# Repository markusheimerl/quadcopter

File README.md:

# quadcopter
A quadcopter simulation & hardware design

Consider a quadcopter modeled as a rigid body with state $(\mathbf{p}, \mathbf{v}, R, \boldsymbol{\omega})$, where $\mathbf{p}, \mathbf{v} \in \mathbb{R}^3$ are the position and linear velocity in the world frame $W$, $R \in SO(3)$ is the body-to-world rotation, and $\boldsymbol{\omega} \in \mathbb{R}^3$ is the angular velocity in the body frame $B$. The world frame is right-handed with $\mathbf{e}_y$ pointing up, and the body frame is defined with $\mathbf{x}_B$ forward, $\mathbf{y}_B$ along the thrust axis, and $\mathbf{z}_B$ to the right. The four rotors sit in an X-configuration at body positions $(x_i, 0, z_i) = (\pm a, 0, \pm a)$, with alternating CCW/CW spin directions $s_i \in \{+1, -1\}$. Each rotor produces a thrust $f_i = k_F \omega_i^2$ along $+\mathbf{y}_B$ and an aerodynamic drag torque $m_i = k_M \omega_i^2$ about $\mathbf{y}_B$. The total body-frame thrust magnitude $T$ and torque $\boldsymbol{\tau} \in \mathbb{R}^3$ are:

$$
\begin{align*}
T &= \sum_{i=0}^{3} k_F \omega_i^2 \\
\tau_x &= \sum_{i=0}^{3} -z_i \, k_F \omega_i^2 \\
\tau_y &= \sum_{i=0}^{3} s_i \, k_M \omega_i^2 \\
\tau_z &= \sum_{i=0}^{3} x_i \, k_F \omega_i^2
\end{align*}
$$

The rigid-body equations of motion are Newton's second law in the world frame and Euler's equation in the body frame. With mass $m$, gravitational acceleration $g$, and diagonal inertia $I = \mathrm{diag}(I_{xx}, I_{yy}, I_{zz})$:

$$
\begin{align*}
\dot{\mathbf{p}} &= \mathbf{v} \\
\dot{\mathbf{v}} &= \tfrac{T}{m} R \mathbf{e}_y - g \mathbf{e}_y \\
\dot{R} &= R [\boldsymbol{\omega}]_\times \\
I \dot{\boldsymbol{\omega}} &= \boldsymbol{\tau} - \boldsymbol{\omega} \times I \boldsymbol{\omega}
\end{align*}
$$

Here $[\boldsymbol{\omega}]_\times$ is the skew-symmetric matrix associated with $\boldsymbol{\omega}$. The simulator integrates these equations at $1\,\mathrm{kHz}$ using a semi-implicit (symplectic) Euler scheme: velocities are advanced first, then positions and attitude are updated with the new velocities. The attitude update uses the exact exponential map on $SO(3)$ with the midpoint angular velocity, evaluated via Rodrigues' formula:

$$
\begin{align*}
\boldsymbol{\phi} &= \tfrac{1}{2} \Delta t (\boldsymbol{\omega}_k + \boldsymbol{\omega}_{k+1}) \\
\mathbf{v}_{k+1} &= \mathbf{v}_k + \Delta t \left( \tfrac{T}{m} R_k \mathbf{e}_y - g \mathbf{e}_y \right) \\
\boldsymbol{\omega}_{k+1} &= \boldsymbol{\omega}_k + \Delta t \, I^{-1} \left( \boldsymbol{\tau} - \boldsymbol{\omega}_k \times I \boldsymbol{\omega}_k \right) \\
\mathbf{p}_{k+1} &= \mathbf{p}_k + \Delta t \, \mathbf{v}_{k+1} \\
R_{k+1} &= R_k \exp\!\left( [\boldsymbol{\phi}]_\times \right) \\
\exp\!\left( [\boldsymbol{\phi}]_\times \right) &= I_3 + \tfrac{\sin\|\boldsymbol{\phi}\|}{\|\boldsymbol{\phi}\|} [\boldsymbol{\phi}]_\times + \tfrac{1 - \cos\|\boldsymbol{\phi}\|}{\|\boldsymbol{\phi}\|^2} [\boldsymbol{\phi}]_\times^2
\end{align*}
$$

For small $\|\boldsymbol{\phi}\|$ the coefficients are replaced by their Taylor expansions $\sin(t)/t \approx 1 - t^2/6$ and $(1-\cos t)/t^2 \approx 1/2 - t^2/24$ to avoid the $0/0$ singularity. A rigid floor constraint clamps $p_y \ge 0$ and zeros downward velocity on contact.

The flight controller is a geometric tracking controller on $SO(3)$ running at $100\,\mathrm{Hz}$, given a target state $\mathbf{x}\_d = (\mathbf{p}\_d, \mathbf{v}\_d, \psi\_d)$. Position and velocity errors drive a desired world-frame force, from which a desired thrust direction $\mathbf{b}\_{2,d}$ is extracted. The thrust magnitude is projected onto the current body-Y axis $\mathbf{b}\_2 = R \mathbf{e}\_y$ to decouple thrust from tilt error:

$$
\begin{align*}
\mathbf{e}_p &= \mathbf{p} - \mathbf{p}_d \\
\mathbf{e}_v &= \mathbf{v} - \mathbf{v}_d \\
\mathbf{F} &= -K_p \mathbf{e}_p - K_v \mathbf{e}_v + m g \mathbf{e}_y \\
\mathbf{b}_{2,d} &= \frac{\mathbf{F}}{\|\mathbf{F}\|} \\
T &= \max\!\left(0,\; \mathbf{F} \cdot \mathbf{b}_2 \right)
\end{align*}
$$

A heading reference $\mathbf{c} = (\cos\psi_d,\, 0,\, -\sin\psi_d)$ defines the desired yaw, and the remaining body axes are obtained by orthogonalization:

$$
\begin{align*}
\mathbf{b}_{3,d} &= \frac{\mathbf{c} \times \mathbf{b}_{2,d}}{\|\mathbf{c} \times \mathbf{b}_{2,d}\|} \\
\mathbf{b}_{1,d} &= \mathbf{b}_{2,d} \times \mathbf{b}_{3,d} \\
R_d &= [\mathbf{b}_{1,d} \;\; \mathbf{b}_{2,d} \;\; \mathbf{b}_{3,d}]
\end{align*}
$$

The attitude and angular-velocity errors in the body frame, together with the feedback-linearized control torque, follow:

$$
\begin{align*}
\mathbf{e}_R &= \tfrac{1}{2} \left( R_d^T R - R^T R_d \right)^{\vee} \\
\mathbf{e}_\omega &= \boldsymbol{\omega} \\
\boldsymbol{\tau} &= -K_R \mathbf{e}_R - K_\omega \mathbf{e}_\omega + \boldsymbol{\omega} \times I \boldsymbol{\omega}
\end{align*}
$$

where $(\cdot)^{\vee}$ is the inverse of $[\cdot]_\times$, extracting the axial vector from a skew-symmetric matrix. Finally, the desired thrust and torque are mapped to squared rotor speeds by inverting the linear X-configuration mixer $[T, \tau_x, \tau_y, \tau_z]^T = M [\omega_0^2, \omega_1^2, \omega_2^2, \omega_3^2]^T$:

$$
\begin{align*}
\omega_0^2 &= \tfrac{T}{4 k_F} - \tfrac{\tau_x}{4 a k_F} + \tfrac{\tau_y}{4 k_M} + \tfrac{\tau_z}{4 a k_F} \\
\omega_1^2 &= \tfrac{T}{4 k_F} - \tfrac{\tau_x}{4 a k_F} - \tfrac{\tau_y}{4 k_M} - \tfrac{\tau_z}{4 a k_F} \\
\omega_2^2 &= \tfrac{T}{4 k_F} + \tfrac{\tau_x}{4 a k_F} + \tfrac{\tau_y}{4 k_M} - \tfrac{\tau_z}{4 a k_F} \\
\omega_3^2 &= \tfrac{T}{4 k_F} + \tfrac{\tau_x}{4 a k_F} - \tfrac{\tau_y}{4 k_M} + \tfrac{\tau_z}{4 a k_F} \\
\omega_i &= \mathrm{clip}\!\left( \sqrt{\max(0, \omega_i^2)},\; \omega_{\min},\; \omega_{\max} \right)
\end{align*}
$$

The commanded rotor speeds are clamped to $[\omega_{\min}, \omega_{\max}]$ before being applied to the dynamics. The implementation runs physics at $1\,\mathrm{kHz}$, control at $100\,\mathrm{Hz}$, and renders frames through a CPU raytracer at $24\,\mathrm{fps}$.

## Hardware

The flight controller / frame PCB lives in [pcb/](pcb/) as a [tscircuit](https://tscircuit.com) design with a JLCPCB-ready build (`npm run fab`). Firmware for it is in [firmware/](firmware/). Older EasyEDA designs are kept in [hardware/](hardware/).

## How to run
### Ubuntu
```bash
sudo apt update
sudo apt install -y clang make git
git clone https://github.com/markusheimerl/quadcopter && cd quadcopter/
make run -j 6
```

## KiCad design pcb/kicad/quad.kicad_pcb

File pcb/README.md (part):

# quad pcb

Flight controller and frame on a single 2‑layer PCB, written in
[tscircuit](https://tscircuit.com). `index.tsx` is the whole design: parts,
schematic, placement and every copper track (drawn by hand, no autorouter).
The four arms are the frame; the electronics sit in the 44.8 mm core. Each
motor connector sits in its corner with the cable opening facing down the arm.

Schematic: [img/schematic.svg](img/schematic.svg) · KiCad files (to look
around, measure, run DRC/ERC): [kicad/](kicad/).

## Order it (no install needed)

The ready‑made files are in [fab/](fab/). On jlcpcb.com:

1. *Order now* → upload `fab/gerbers.zip`. The viewer should show a
   75.12 × 75.12 mm, 2‑layer board with the USB‑C slots drawn. 1.6 mm, FR‑4,
   any colour. Via covering: *tented* (the default). Surface finish: the
   form defaults to leaded HASL – pick lead‑free HASL, or ENIG (flatter pads
   for the IMU's 0.5 mm LGA). *Remove order number*: choose *Specify a
   location* – the back has a `JLCJLCJLCJLC` spot for it.
2. Tick *PCB Assembly*, top side, **Standard** (the ESP32 module and the IMU
   are Standard‑only; about $170 for assembly and parts of 5 boards, Sep
   2026). Upload `fab/bom.csv` and `fab/cpl.csv`. Every row has its JLCPCB
   part number and all are in stock. Seven are *extended* parts (module,
   IMU, TPS63001, inductor, the three connector types), the rest *basic* or
   *preferred* – which only matters for Economic PCBA: Standard charges the
   same feeder fee (about $1.53) for each of the 26 BOM lines. Tick *Confirm
   production file* and look at the panel drawing before it goes into
   production.
3. Order remark: "The ESP32 module and the USB‑C socket overhang the nose
   and tail edges on purpose. Break‑off tabs only on the end faces of the
   arms – none on the curved core outline (the motor connectors, C13 and
   both buttons are within 0.45 mm of it). Please cut the stencil from our
   F_Paste layer." Standard PCBA always adds rails and fiducials; file the
   tab nubs at the arm tips flush before fitting the motor clips.
4. In the placement preview check each part once: antenna toward the nose,
   USB‑C opening at the tail edge, the diode bands (cathode) on the inner end
   of D1–D4 where each diode meets its VBAT rail, LED anodes toward their 1 k
   resistor (LED1 → R11, LED2 → R17), the IMU's pin‑1 dot (top‑left corner),
   U3's pin 1 at the silkscreen dot (top‑left, toward the inductor), U4 pin 1.
   `cpl.csv` already places every part at JLCPCB's own footprint origin.

## What is on it

| Block | Part | JLCPCB # |
|---|---|---|
| MCU | ESP32‑S3‑WROOM‑1‑N16R8, antenna over the nose edge | C2913202 |
| IMU | BMI323, I2C at 0x68, +X = nose, +Y = left, +Z = up | C5368700 |
| Motor drive ×4 | AO3400A low‑side, 47 Ω gate, 10 k pull‑down, B5819W flyback | C20917, C8598 |
| Motor connectors ×4 | HC‑1.25‑2PWT (1.25 mm, 2 pin), "+" marked on the silkscreen | C2845379 |
| Battery | Molex PicoBlade 53398‑0271, "+"/"−" marked, 100 µF bulk | C122410, C15008 |
| 3.3 V | TPS63001 buck‑boost: 3.3 V from 1.8–5.5 V in (1.2 A buck, 0.8 A boost), always on, power‑save mode at light load, 2.2 µH | C28060, C5832372 |
| Charger | TP4054, 190 mA (R16 = 5.1 k, datasheet formula 1), CHG LED | C32574 |
| USB | USB‑C, native S3 USB (flashing + console), 5.1 k CC pull‑downs | C2765186 |
| Buttons | RST (EN, left edge) and BOOT (IO0, right edge), top‑actuated | C720477 |
| Battery sense | VBAT / 2 on IO10 (100 k / 100 k, 100 nF) | |
| UART pads | TX, RX, GND on the back (TP1–TP3) | |

Pin map (also on the schematic, and in `firmware/main/main.c`):

| GPIO | Use |
|---|---|
| IO1, IO2, IO16, IO4 | PWM0–3 → M0 front right, M1 back right, M2 back left, M3 front left (high = on) |
| IO11, IO12 | I2C SDA, SCL (BMI323) |
| IO10 | battery voltage / 2 (ADC1 channel 9, use 12 dB attenuation) |
| IO21 | LED1, active low |
| IO19, IO20 | USB D−, D+ |
| IO0 / EN | BOOT / RESET buttons |
| TXD0, RXD0 | UART0 pads TP1, TP2 |

Motors: FR and BL spin CCW, BR and FL spin CW (printed on each arm). The
connector pin marked "+" is VBAT; the other pin is switched to ground. The
pinout and the connector positions match the May 2026 board, so its motor
leads plug in the same way and reach just as far: each connector sits as far
out along its arm as its metal side tabs allow (0.33 mm from the curved
edge), its opening about 24.8 mm from the arm tip.
A brushed motor's direction follows its polarity – if one spins the wrong
way, swap its two wires.

Copper: bottom layer is a ground pour; VBAT runs 1 mm wide on top plus a
1.5 mm bus on the bottom from the battery connector; motor nets 0.6–0.8 mm;
vias 0.3/0.6 mm. The buck‑boost follows its datasheet layout: input and
output caps right at VIN/VOUT with their grounds straight into the exposed
pad, the inductor beside the VBAT rail, unbroken ground pour underneath
(the USB data pair runs past it, between converter and IMU).

The motor connectors' "+" pins match the May 2026 boards. The November 2025
board had front‑left and back‑right the other way round: leads made for that
board spin FL/BR backwards here. Check each motor's direction with the props
off (BLE keys `1`–`4`).

## Change the design

Needs Node ≥ 20; `npm install` brings everything else (including `bun`) and
applies the small tscircuit fixes in `scripts/patch-tscircuit.mjs`.

```bash
cd pcb
npm install
npm run build   # ~10 s: dist/circuit.json (board) + dist/sch.circuit.json (schematic), then DRC
npm run fab     # fab/gerbers.zip, fab/bom.csv, fab/cpl.csv
npm run kicad   # kicad/quad.kicad_pcb, .kicad_sch, .kicad_pro
npm run img     # img/pcb.png, img/schematic.svg
npm run place   # placement only (no copper) -> img/place.png
npm run dev     # live PCB / schematic / 3D view at http://localhost:3020
```

* `build.tsx` replaces `tsci build` (whose built‑in checks can hang). It
  renders the board twice: once with the copper for the PCB, once without it
  for the schematic, since tscircuit would otherwise draw the hand‑made PCB
  tracks into the schematic.
* `scripts/silk.ts` drops unprintable footprint texts and clips silkscreen
  lines 0.15 mm off pads, holes and the board edge (what JLCPCB would clip).
* `scripts/jlc.ts` writes the BOM and a CPL at JLCPCB's footprint origins
  (tscircuit's own pick‑and‑place uses pad centres, which is off for the
  module, USB‑C and connectors). `npm run fab` also puts each USB‑C slot's
  `G85` on one line in the drill file, as Excellon wants it.
* The exposed pad of U3 gets TI's stencil (two 1.5 × 1.06 mm openings at
  ±0.63 mm, 80 %)
  instead of a full opening, so the part doesn't float (`build.tsx`).
* `scripts/kicad.ts` touches up the KiCad export so KiCad reads it right:
  real power symbols, correct diode/connector pin numbers, net ties at
  junctions, no‑connect flags, JLCPCB design rules, text sizes as printed.
  The ground pour comes without fill: press **B** in KiCad to fill it.
* `footprints/` caches the JLCPCB footprints (some edited: USB‑C slots,
  a connector courtyard, TPS63001 exposed pad as TI's 1.65 × 2.4 mm land,
  inductor pads as its maker recommends),
  so builds work offline.
* `drc.py` is an independent check (`pip install shapely`): 0.2 mm copper
  clearance, 0.3 mm to the edge, via sizes, and that every net is one piece
  of copper: `python3 drc.py`.

## Checked before release

* tscircuit DRC (routing, placement, netlist, JLCPCB rules) and `drc.py`: clean.
* KiCad 9 DRC on the exported board with JLCPCB limits, zones refilled: clean;
  KiCad ERC on the schematic: clean.
* The netlist KiCad computes from the drawn schematic, and the connectivity
  extracted from the gerber copper + drill files, both equal the design
  netlist pin for pin (no opens, no shorts).
* Silkscreen in the gerbers: ≥ 0.15 mm from every pad and hole. Labels print
  about 1.0 mm tall with ≥ 0.16 mm strokes (BOOT 0.75 mm: it sits between a
  via and the edge); the "+"/"−" polarity marks are 1.0–1.2 mm lines.
* Every part checked against its datasheet (pinout vs footprint vs netlist,
  application circuit, ratings), each finding re‑checked independently.

## First power‑up

1. Meter every battery lead before its first plug‑in. Under the battery
   socket the silkscreen reads "+ − BAT": the pin above the "+" (the one
   farther from `BAT`) must get the pack's +. A reversed pack destroys the
   board. Motors go into the four arm sockets, the battery only into the
   `BAT` socket: a battery plug fits a motor socket too, and in two of them
   it shorts the pack through a diode.
2. Props off. Plug the battery in: LED1 blinks at 1 Hz within about 2 s
   (5 Hz: IMU not found; dark: the pack is below 3.0 V and the board sleeps
   – charge it – or look for a short or a dead 3.3 V). Nothing spins at
   power‑up.
3. Connect with `firmware/tools/motor_keys.py` (`pip install bleak`). It
   prints the status (reset reason, IMU id `0x..43`, level calibration,
   battery mV, trim, gain); `?` repeats it. The level calibration runs as soon as the
   board lies still and within 5° of level for 1 s; if it was moved or on a
   slope then, set it on a level surface and press `c`.
4. Tilt by hand and watch the log: `r` goes positive with the right side
   down, `p` positive with the nose down.
5. Keys `1`–`4` spin M0 (front right), M1 (back right), M2 (back left) and
   M3 (front left) for 1 s. Viewed from above, M0 and M2 must turn CCW and M1
   and M3 CW; swap a motor's two wires if not.
6. Still without props: `a` (arm), a few `w`, then tilt the board – the
   motors on the lower side speed up. `d` disarms. Keep a hand on it.
7. First hover, over a soft floor with room around it: `a`, then `w` until
   the quad gets light and lifts off. If it isn't light by throttle ≈ 185,
   stop: motors or props too small for its weight. Keep it about 30 cm up
   with `w`/`x` and hold it in place with the arrow keys (a press tilts it
   4° that way for 0.7 s; hold the key to keep going). It holds itself
   level, not in place: like any toy quad it drifts, and you steer against
   that. Climb briskly off the floor (one `w` more than it needs to lift),
   and after touching down take the throttle to 0 before the next take‑off:
   the integrators need to see the lift‑off (`air` in the log).
8. If it keeps drifting the same way, trim after landing: `i` `k` `j` `l`
   (forward, back, left, right, 0.5° per press) toward where it should go,
   e.g. `i` a few times when it drifts backward. Trim adds to the level
   found at power‑up, so always power up (or press `c`) on a level floor.
9. Fast wobble or buzz: lower the gain with `[`. Slow rocking, overshoot or
   a soft feel: raise it with `]` (×1.25 per press). Trim and gain are
   saved on the drone. The log's `I` columns show how much the integrators
   correct: roll or pitch near ±25 means the weight is far off centre (move
   the battery). Until the log says `air` they stop at ±7.5.

## Limits worth knowing

* **Brown‑outs:** the buck‑boost holds 3.3 V while the battery sags as low
  as 1.8 V, so motor current can no longer reset the ESP32 (the old boards
  fed it from an LDO, or from the motor rail itself). The firmware logs the
  reset reason at boot; `BROWN-OUT` there would mean something else is wrong.
* **Packs:** fly RC LiPos without a protection board, rated for the 2–6 A
  the four motors pull (6 A is 35 C from 170 mAh, 24 C from 250 mAh). A
  phone‑type cell with a protection PCB, such as a generic LP502030
  "250 mAh", is made for about 0.5 C, and its protection typically cuts off
  at 2–3 A: it can switch the whole board off in flight. That looks like a
  brown‑out, but after re‑plugging the reset reason reads 1 (power‑on),
  not `BROWN-OUT`. Keep such cells for the bench.
* **Low battery:** because the ESP32 keeps running on a nearly empty pack,
  only the firmware protects it: it logs VBAT (IO10) with every status line,
  warns below 3.3 V while armed and won't arm below 3.5 V. Disarmed below
  3.3 V for 10 s (or below 3.0 V for 1 s) it goes to deep sleep (about 0.1 mA
  for the whole board, the converter in power‑save mode) and checks again
  every 5 minutes (every 30 below 3.0 V); above 3.5 V (e.g. after charging
  over USB) it starts
  normally (press RST to skip the wait). To flash a board that is asleep,
  hold BOOT and tap RST. Running and idle it draws about 50 mA, so a pack
  left plugged in is down to 3.3 V within hours – unplug it after flying.
* **Battery connector (the one real compromise):** PicoBlade contacts are
  rated 1 A, but CN5 carries all four motors – 2–6 A in flight, more at
  spin‑up. It was kept so your existing packs and the May 2026 board's leads
  fit. Expect some extra sag and a warm connector; for hard flying, solder a
  22–24 AWG pigtail with a BT2.0/XT30 plug instead. The 1.25 mm motor
  connectors (also 1 A) are within rating up to about 1 A per motor.
* No reverse‑polarity protection on the battery and no ESD protection on
  USB: see *First power‑up*.
* **Charging:** 190 mA from the charger, of which the running board takes
  about 50 mA: about 140 mA into the pack, and the full 190 mA while a flat
  pack charges with the board asleep – about 1 C for the 170 mAh pack, less
  for 250 mAh. For a pack of 300 mAh or more, R16 = 3.3 k (C25890) gives
  260 mA. There is no temperature sensing: charge attended. While the ESP32
  runs, the charger doesn't terminate (the board draws more than its 19 mA
  end‑of‑charge current), so the CHG LED stays on even when the pack is full
  and the pack is held at 4.2 V: unplug USB once the pack has had time to
  fill (about 1.2 h for 170 mAh, 1.8 h for 250 mAh from empty). Never store a pack plugged in – even asleep the
  board takes it below 3.0 V within days – and don't recharge a pack found
  below about 2.5 V.
* The board may not start from USB alone (the charger only trickles into an
  empty VBAT): plug a charged battery in first, then USB, to flash.
* Firmware (`firmware/main/main.c`): the motors are driven in two phases
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
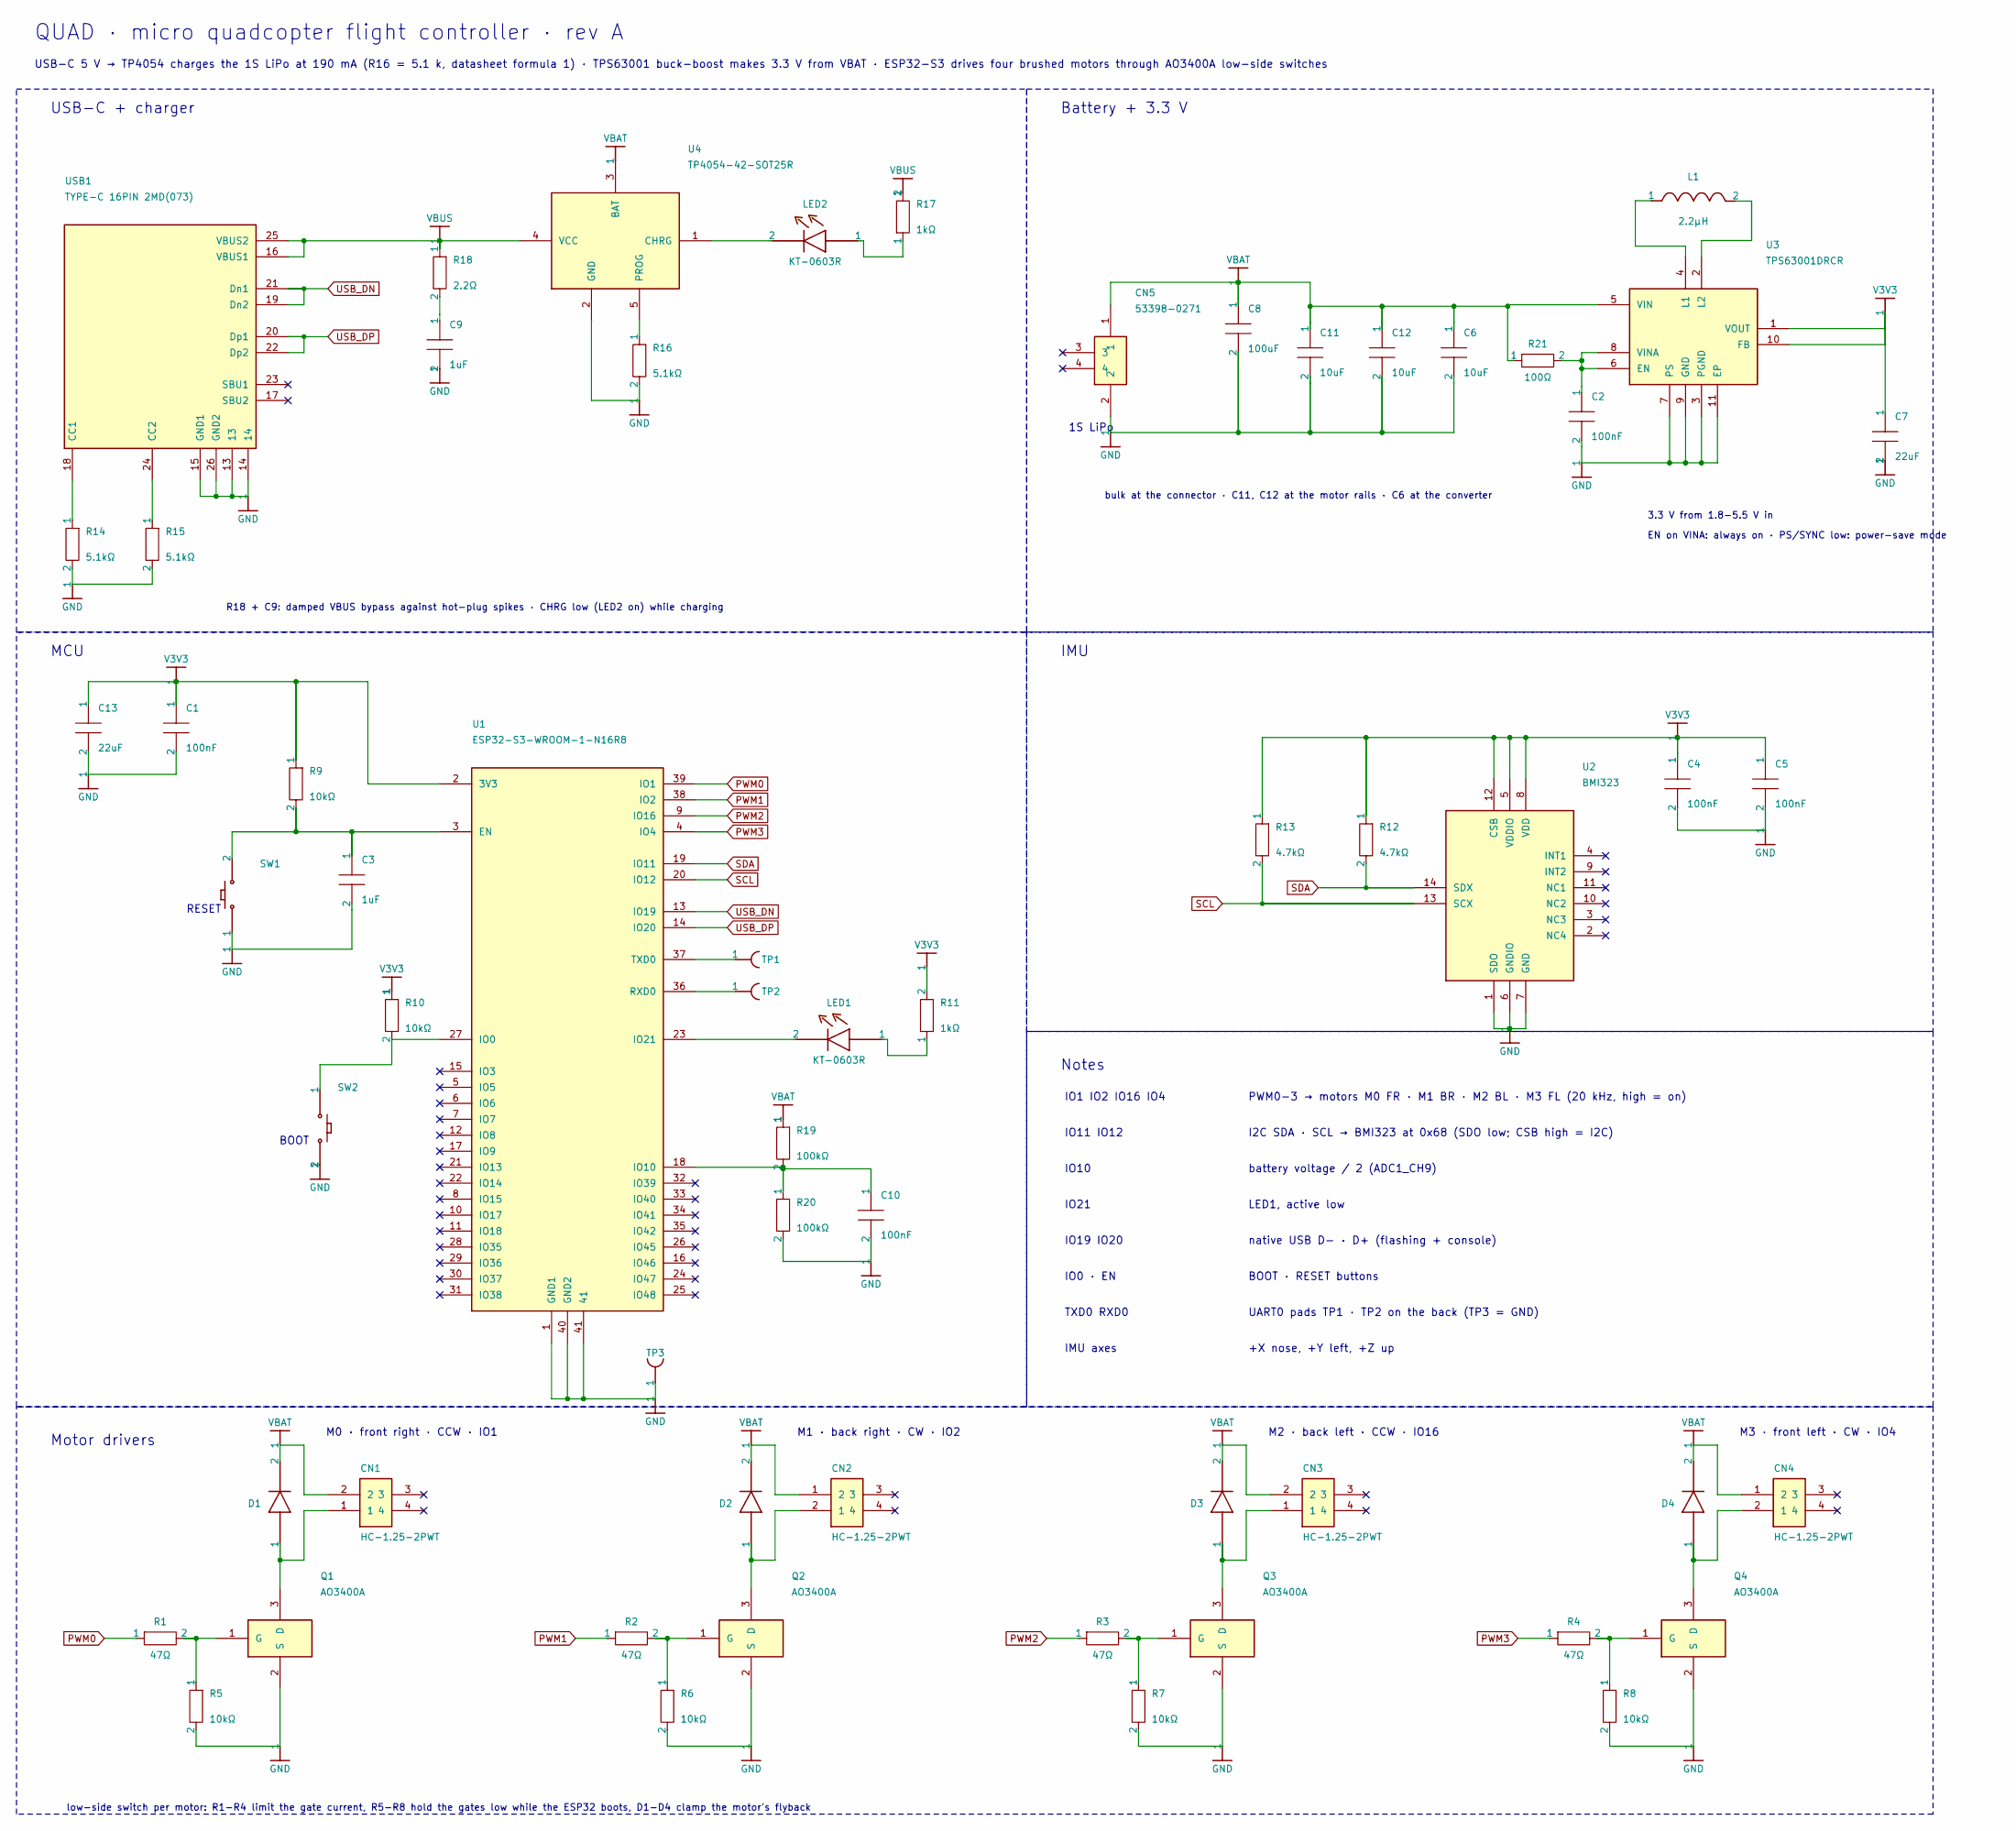
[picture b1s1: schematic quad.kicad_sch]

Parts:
C1, C2, C4, C5, C10: 100nF
C3, C9: 1uF
C6, C11, C12: 10uF
C7, C13: 22uF
C8: 100uF
CN1, CN2, CN3, CN4: HC-1.25-2PWT
CN5: 53398-0271
D1, D2, D3, D4: B5819W
L1: 2.2µH
LED1, LED2: KT-0603R
Q1, Q2, Q3, Q4: AO3400A
R1, R2, R3, R4: 47Ω
R5, R6, R7, R8, R9, R10: 10kΩ
R11, R17: 1kΩ
R12, R13: 4.7kΩ
R14, R15, R16: 5.1kΩ
R18: 2.2Ω
R19, R20: 100kΩ
R21: 100Ω
SW1: SW1
SW2: SW2
TP1: TP1
TP2: TP2
TP3: TP3
U1: ESP32-S3-WROOM-1-N16R8
U2: BMI323
U3: TPS63001DRCR
U4: TP4054-42-SOT25R
USB1: TYPE-C 16PIN 2MD(073)

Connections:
CC1: R14.1, USB1.18 (CC1)
CC2: R15.1, USB1.24 (CC2)
CHG_A: LED2.1, R17.1
CHRG: LED2.2, U4.1 (CHRG)
EN: C3.1, R9.2, SW1.2, U1.3 (EN)
G0: Q1.1 (G), R1.2, R5.1
G1: Q2.1 (G), R2.2, R6.1
G2: Q3.1 (G), R3.2, R7.1
G3: Q4.1 (G), R4.2, R8.1
GND: C1.2, C2.2, C3.2, C4.2, C5.2, C6.2, C7.2, C8.2, C9.2, C10.2, C11.2, C12.2, C13.2, CN5.2, Q1.2 (S), Q2.2 (S), Q3.2 (S), Q4.2 (S), R5.2, R6.2, R7.2, R8.2, R14.2, R15.2, R16.2, R20.2, SW1.1, SW2.2, TP3.1, U1.1 (GND1), U1.40 (GND2), U1.41, U2.1 (SDO), U2.6 (GNDIO), U2.7 (GND), U3.3 (PGND), U3.7 (PS), U3.9 (GND), U3.11 (EP), U4.2 (GND), USB1.13, USB1.14, USB1.15 (GND1), USB1.26 (GND2)
IO0: R10.2, SW2.1, U1.27 (IO0)
LED: LED1.2, U1.23 (IO21)
LED_A: LED1.1, R11.1
LX1: L1.1, U3.4 (L1)
LX2: L1.2, U3.2 (L2)
M0: CN1.1, D1.2 (1), Q1.3 (D)
M1: CN2.2 (1), D2.2 (1), Q2.3 (D)
M2: CN3.1, D3.2 (1), Q3.3 (D)
M3: CN4.2 (1), D4.2 (1), Q4.3 (D)
PROG: R16.1, U4.5 (PROG)
PWM0: R1.1, U1.39 (IO1)
PWM1: R2.1, U1.38 (IO2)
PWM2: R3.1, U1.9 (IO16)
PWM3: R4.1, U1.4 (IO4)
RXD0: TP2.1, U1.36 (RXD0)
SCL: R13.2, U1.20 (IO12), U2.13 (SCX)
SDA: R12.2, U1.19 (IO11), U2.14 (SDX)
TXD0: TP1.1, U1.37 (TXD0)
USB_DN: U1.13 (IO19), USB1.19 (Dn2), USB1.21 (Dn1)
USB_DP: U1.14 (IO20), USB1.20 (Dp1), USB1.22 (Dp2)
V3V3: C1.1, C4.1, C5.1, C7.1, C13.1, R9.1, R10.1, R11.2, R12.1, R13.1, U1.2 (3V3), U2.5 (VDDIO), U2.8 (VDD), U2.12 (CSB), U3.1 (VOUT), U3.10 (FB)
VBAT: C6.1, C8.1, C11.1, C12.1, CN1.2, CN2.1 (2), CN3.2, CN4.1 (2), CN5.1, D1.1 (2), D2.1 (2), D3.1 (2), D4.1 (2), R19.1, R21.1, U3.5 (VIN), U4.3 (BAT)
VBUS: R17.2, R18.1, U4.4 (VCC), USB1.16 (VBUS1), USB1.25 (VBUS2)
VBUS_C: C9.1, R18.2
VINA: C2.1, R21.2, U3.6 (EN), U3.8 (VINA)
VSENSE: C10.1, R19.2, R20.1, U1.18 (IO10)

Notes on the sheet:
QUAD · micro quadcopter flight controller · rev A
USB-C 5 V → TP4054 charges the 1S LiPo at 190 mA (R16 = 5.1 k, datasheet formula 1) · TPS63001 buck-boost makes 3.3 V from VBAT · ESP32-S3 drives four brushed motors through AO3400A low-side switches
USB-C + charger
Battery + 3.3 V
MCU
IMU
Notes
IO1 IO2 IO16 IO4
PWM0-3 → motors M0 FR · M1 BR · M2 BL · M3 FL (20 kHz, high = on)
IO11 IO12
I2C SDA · SCL → BMI323 at 0x68 (SDO low; CSB high = I2C)
IO10
battery voltage / 2 (ADC1_CH9)
IO21
LED1, active low
IO19 IO20
native USB D- · D+ (flashing + console)
IO0 · EN
BOOT · RESET buttons
TXD0 RXD0
UART0 pads TP1 · TP2 on the back (TP3 = GND)
IMU axes
+X nose, +Y left, +Z up
1S LiPo
bulk at the connector · C11, C12 at the motor rails · C6 at the converter
3.3 V from 1.8-5.5 V in
EN on VINA: always on · PS/SYNC low: power-save mode
R18 + C9: damped VBUS bypass against hot-plug spikes · CHRG low (LED2 on) while charging
low-side switch per motor: R1-R4 limit the gate current, R5-R8 hold the gates low while the ESP32 boots, D1-D4 clamp the motor's flyback
Motor drivers
M0 · front right · CCW · IO1
M1 · back right · CW · IO2
M2 · back left · CCW · IO16
M3 · front left · CW · IO4
RESET
BOOT

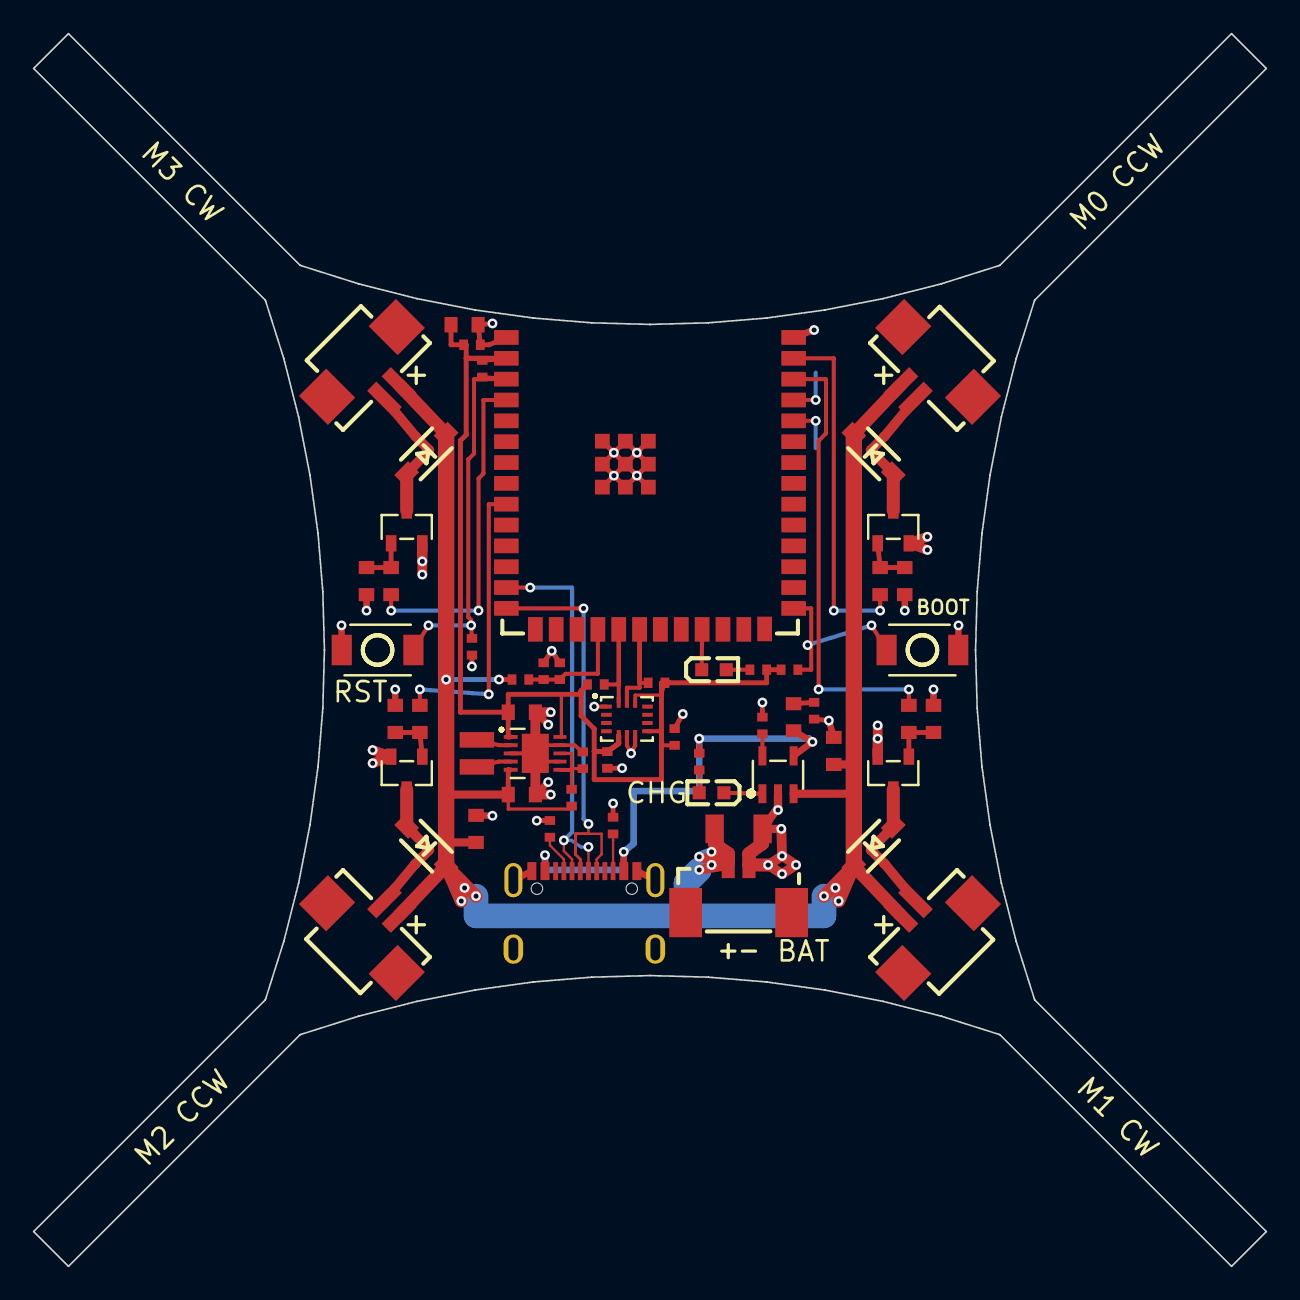
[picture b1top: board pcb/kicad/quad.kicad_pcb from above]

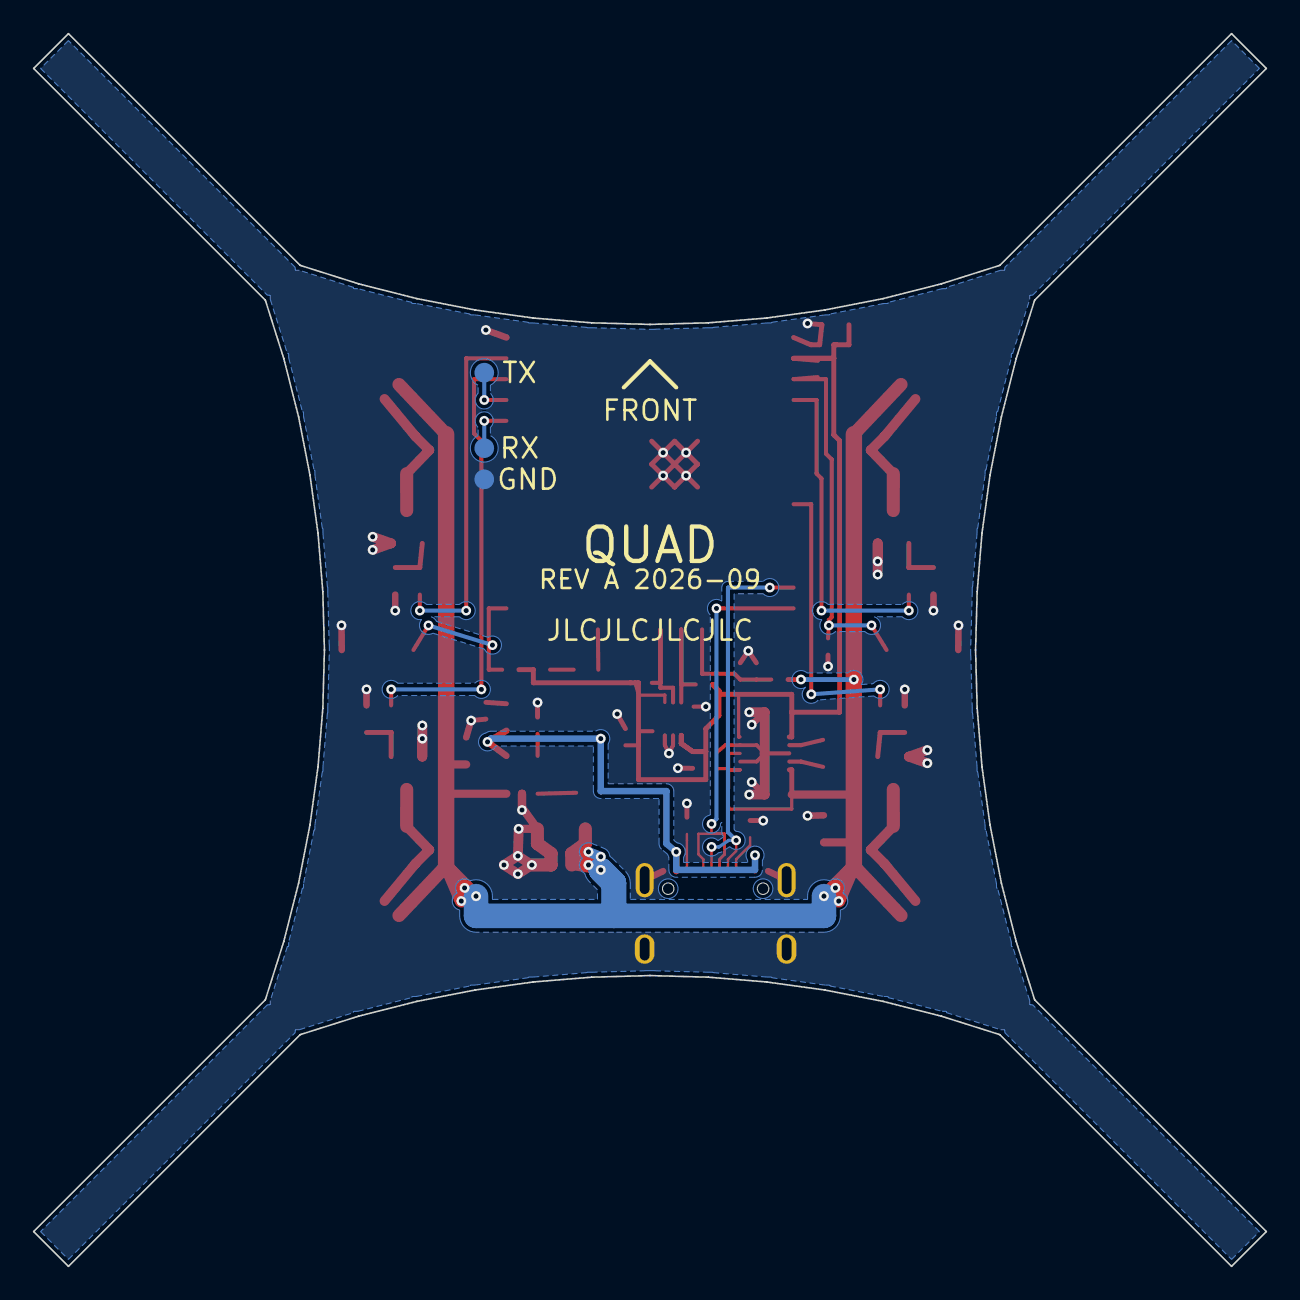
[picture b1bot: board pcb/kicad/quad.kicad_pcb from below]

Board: 2 copper layers, 75.1 x 75.1 mm, 60 parts (3 on the bottom side), 36 nets.

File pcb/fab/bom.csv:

"Comment","Designator","Footprint","JLCPCB Part #"
"100nF","C1,C2,C4,C5,C10","0402","C1525"
"1uF","C3,C9","0402","C52923"
"10uF","C6,C11,C12","0603","C19702"
"22uF","C7,C13","0603","C59461"
"100uF","C8","1206","C15008"
"HC-1.25-2PWT","CN1,CN2,CN3,CN4","C2845379","C2845379"
"53398-0271","CN5","C122410","C122410"
"B5819W","D1,D2,D3,D4","C8598","C8598"
"FTC252012S2R2MBCA","L1","C5832372","C5832372"
"KT-0603R","LED1,LED2","C2286","C2286"
"AO3400A","Q1,Q2,Q3,Q4","C20917","C20917"
"47R","R1,R2,R3,R4","0603","C23182"
"10k","R5,R6,R7,R8","0603","C25804"
"10k","R9,R10","0402","C25744"
"1k","R11,R17","0402","C11702"
"4.7k","R12,R13","0402","C25900"
"5.1k","R14,R15,R16","0402","C25905"
"2.2R","R18","0603","C22939"
"100k","R19,R20","0402","C25741"
"100R","R21","0402","C25076"
"TS-1088-AR02016","SW1,SW2","C720477","C720477"
"ESP32-S3-WROOM-1-N16R8","U1","C2913202","C2913202"
"BMI323","U2","C5368700","C5368700"
"TPS63001DRCR","U3","C28060","C28060"
"TP4054-42-SOT25R","U4","C32574","C32574"
"TYPE-C 16PIN 2MD(073)","USB1","C2765186","C2765186"

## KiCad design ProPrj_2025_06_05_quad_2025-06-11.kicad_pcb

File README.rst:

drone
=====
A design of a tiny drone

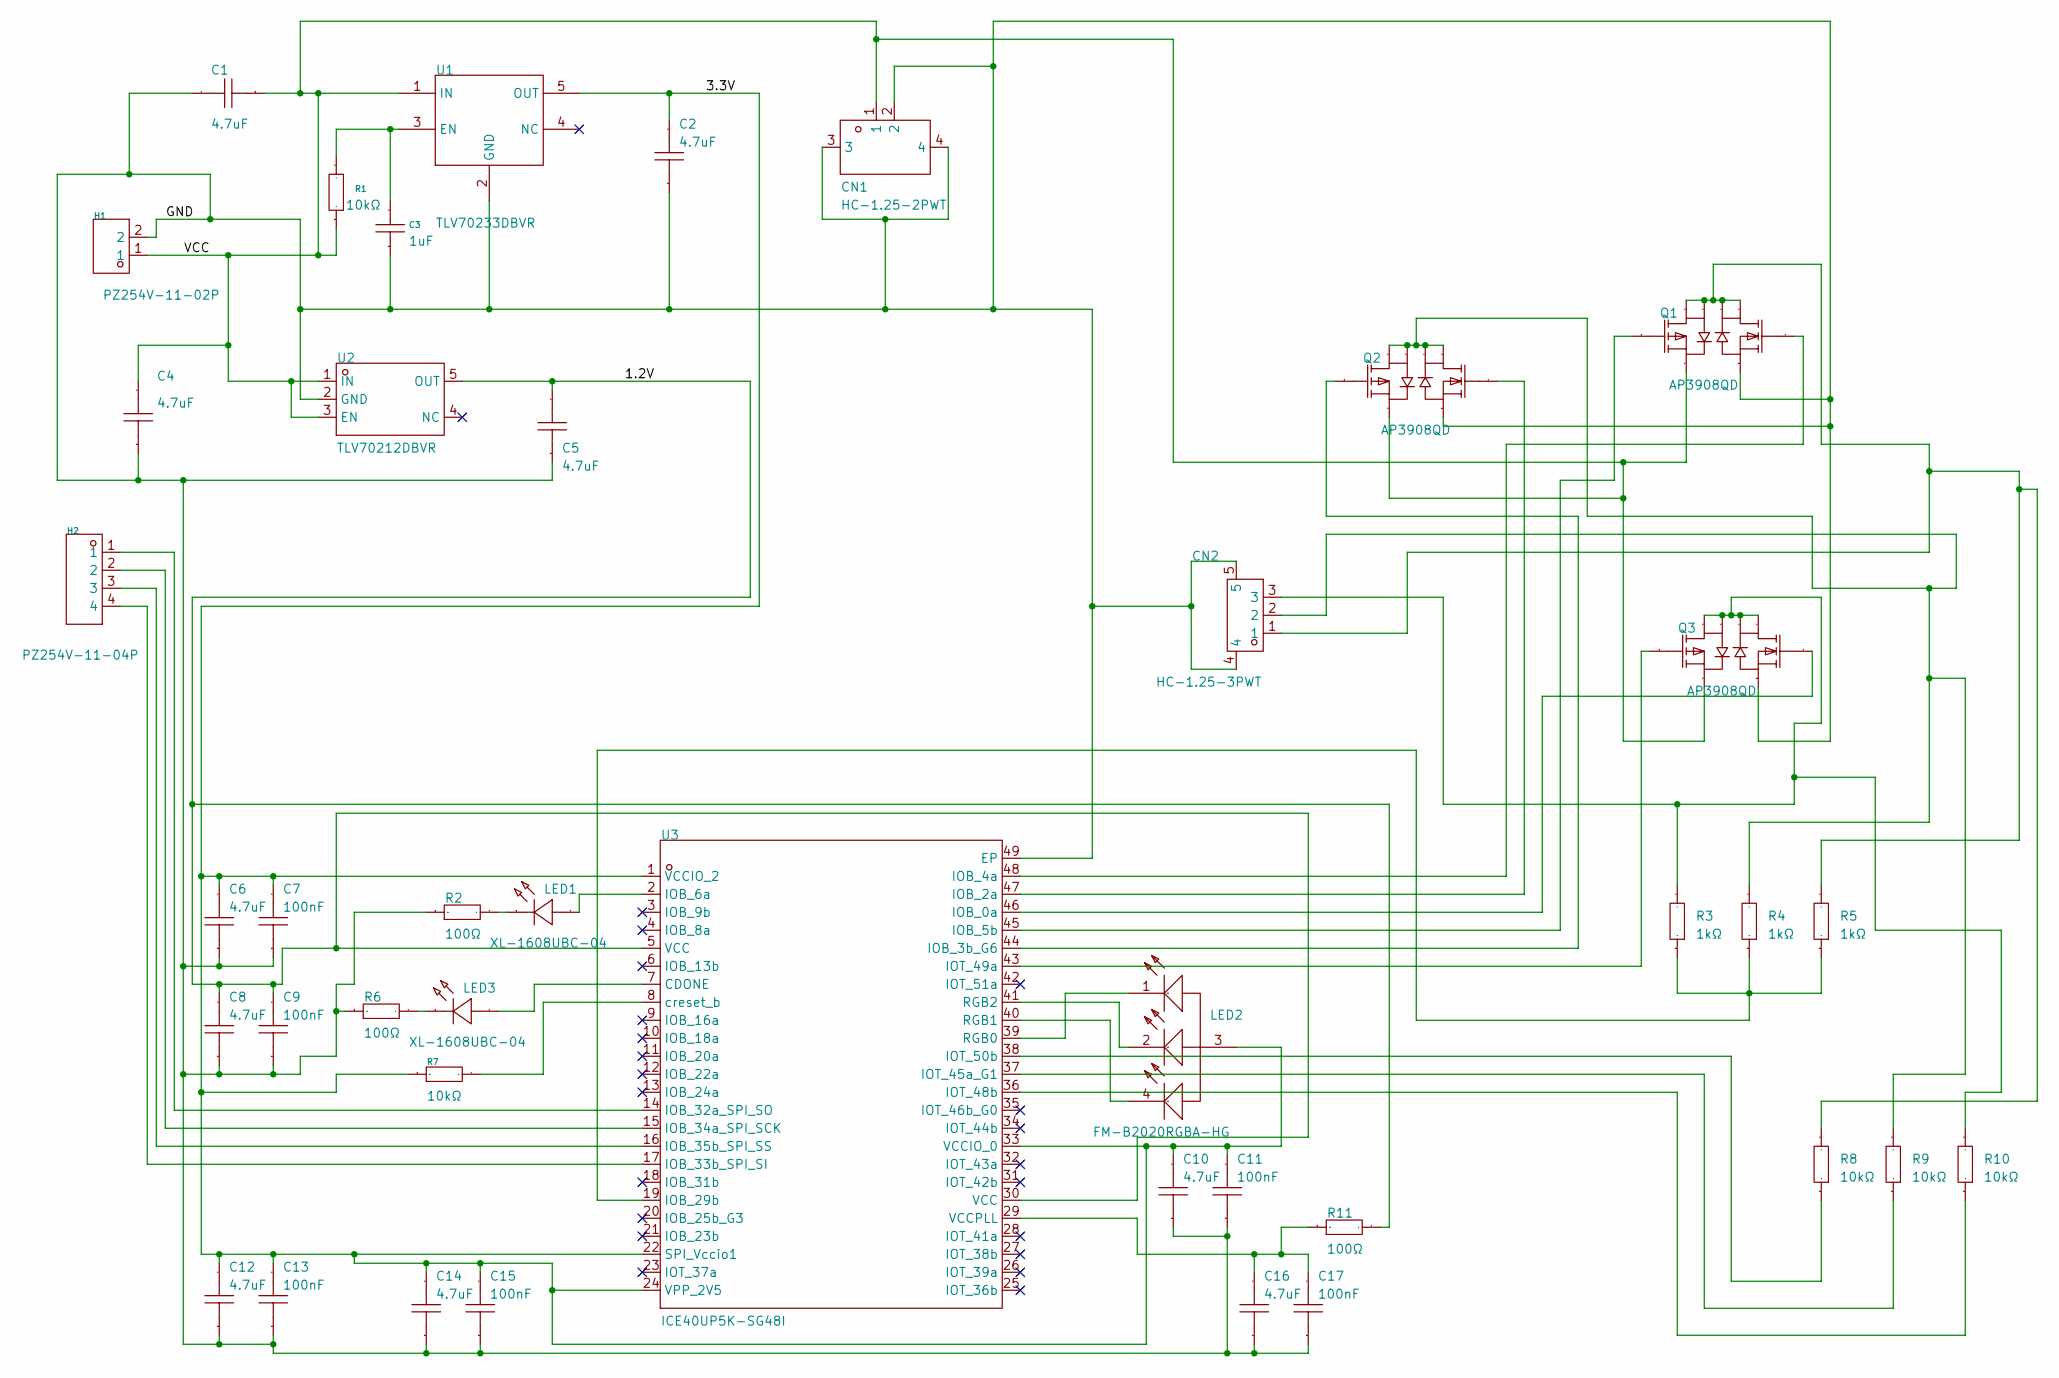
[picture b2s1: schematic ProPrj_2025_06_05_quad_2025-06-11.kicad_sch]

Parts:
C1, C2, C4, C5, C6, C8, C10, C12, C14, C16: 4.7uF; C0402; Manufacturer Part CL05A475MQ5NRNC; LCSC Part Name 4.7uF ±20% 6.3V
C3: 1uF; C0402; Manufacturer Part CL05A105KO5NNNC; LCSC Part Name 1uF ±10% 16V
C7, C9, C11, C13, C15, C17: 100nF; C0402; Manufacturer Part CL05B104KO5NNNC; LCSC Part Name 100nF ±10% 16V
CN1: HC-1.25-2PWT; CONN-SMD_2P-P1.25-HC-1.25-2PWT; Manufacturer Part HC-1.25-2PWT; LCSC Part Name 1x2P 间距:1.25mm 卧贴 系列:PicoBlade(MX 1.25)
CN2: HC-1.25-3PWT; CONN-SMD_HC-1.25-3PWT; Manufacturer Part HC-1.25-3PWT; LCSC Part Name 1x3P 间距:1.25mm 卧贴 系列:PicoBlade(MX 1.25)
H1: PZ254V-11-02P; HDR-TH_2P-P2.54-V-M; Manufacturer Part PZ254V-11-02P; LCSC Part Name 间距:2.54mm 1x2P 直插 方针
H2: PZ254V-11-04P; HDR-TH_4P-P2.54-V-M; Manufacturer Part PZ254V-11-04P; LCSC Part Name 间距:2.54mm 1x4P 直插 方针
LED1, LED3: XL-1608UBC-04; LED0603-RD_BLUE; Manufacturer Part XL-1608UBC-04; LCSC Part Name XL-1608UBC-04
LED2: FM-B2020RGBA-HG; LED-SMD_FM-B2020RGBA-HG; Manufacturer Part FM-B2020RGBA-HG; LCSC Part Name FM-B2020RGBA-HG
Q1, Q2, Q3: AP3908QD; DFN-8_L3.1-W3.2-P0.65-BL-EP; Manufacturer Part AP3908QD; LCSC Part Name N/P沟道,电流:20A,耐压:30V
R1, R7: 10kΩ; R0402; Manufacturer Part 0402WGJ0103TCE; LCSC Part Name 10kΩ ±5% 62.5mW 厚膜电阻
R2, R6, R11: 100Ω; R0402; Manufacturer Part RC0402FR-07100RL; LCSC Part Name 厚膜电阻 100Ω ±1% 62.5mW
R3, R4, R5: 1kΩ; R0603; Manufacturer Part 0603WAF1001T5E; LCSC Part Name 1kΩ ±1% 100mW 厚膜电阻
R8, R9, R10: 10kΩ; R0603; Manufacturer Part RC0603FR-0710KL; LCSC Part Name 厚膜电阻 10kΩ ±1% 100mW
U1: TLV70233DBVR; SOT-23-5_L3.0-W1.7-P0.95-LS2.8-BR; Manufacturer Part TLV70233DBVR; LCSC Part Name 具有使能功能的 300mA、高 PSRR、低 IQ、低压降稳压器
U2: TLV70212DBVR; SOT-23-5_L3.0-W1.7-P0.95-LS2.8-BL; Manufacturer Part TLV70212DBVR; LCSC Part Name 具有使能功能的 300mA、高 PSRR、低 IQ、低压降稳压器
U3: ICE40UP5K-SG48I; QFN-48_L7.0-W7.0-P0.50-TL-EP5.4-1; Manufacturer Part ICE40UP5K-SG48I; LCSC Part Name ICE40UP5K SG48I

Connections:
1.2V: C5.2, C8.2, C9.2, R11.2, U2.5 (OUT), U3.5 (VCC), U3.30 (VCC)
3.3V: C2.2, C6.2, C7.2, C10.2, C11.2, C12.2, C13.2, C14.2, C15.2, LED2.3 (A), R7.1, U1.5 (OUT), U3.1 (VCCIO_2), U3.22 (SPI_Vccio1), U3.24 (VPP_2V5), U3.33 (VCCIO_0)
$1N1858: H2.2, U3.15 (IOB_34a_SPI_SCK)
$1N1859: H2.3, U3.16 (IOB_35b_SPI_SS)
$1N1860: H2.4, U3.17 (IOB_33b_SPI_SI)
$1N1861: C16.2, C17.2, R11.1, U3.29 (VCCPLL)
$1N1862: R7.2, U3.8 (creset_b)
$1N1863: LED3.1 (K), R6.2
$1N1864: LED2.2 (K), U3.41 (RGB2)
$1N1865: LED2.4 (K), U3.40 (RGB1)
$1N1866: LED2.1 (K), U3.39 (RGB0)
$1N1867: LED3.2 (A), U3.7 (CDONE)
$1N1868: H2.1, U3.14 (IOB_32a_SPI_SO)
$1N1873: C3.2, R1.2, U1.3 (EN)
$1N1874: LED1.2 (A), U3.2 (IOB_6a)
$1N1875: LED1.1 (K), R2.2
$1N1876: Q1.2 (G), U3.48 (IOB_4a)
$1N1877: Q2.2 (G), U3.47 (IOB_2a)
$1N1878: CN2.3, Q3.5 (D), Q3.6 (D), Q3.7 (D), Q3.8 (D), R3.2, R10.2
$1N1879: CN2.1, Q1.5 (D), Q1.6 (D), Q1.7 (D), Q1.8 (D), R5.2, R8.2
$1N1880: Q3.2 (G), U3.46 (IOB_0a)
$1N1881: Q1.4 (G), U3.45 (IOB_5b)
$1N1882: Q2.4 (G), U3.44 (IOB_3b_G6)
$1N1883: Q3.4 (G), U3.43 (IOT_49a)
$1N1884: R3.1, R4.1, R5.1, U3.19 (IOB_29b)
$1N1890: CN2.2, Q2.5 (D), Q2.6 (D), Q2.7 (D), Q2.8 (D), R4.2, R9.2
$1N1897: R8.1, U3.38 (IOT_50b)
$1N1905: R10.1, U3.36 (IOT_48b)
$1N1908: R9.1, U3.37 (IOT_45a_G1)
GND: C1.2, C2.1, C3.1, C4.1, C5.1, C6.1, C7.1, C8.1, C9.1, C10.1, C11.1, C12.1, C13.1, C14.1, C15.1, C16.1, C17.1, CN1.2, CN1.3, CN1.4, CN2.4, CN2.5, H1.2, Q1.1 (S), Q2.1 (S), Q3.1 (S), R2.1, R6.1, U1.2 (GND), U2.2 (GND), U3.49 (EP)
VCC: C1.1, C4.2, CN1.1, H1.1, Q1.3 (S), Q2.3 (S), Q3.3 (S), R1.1, U1.1 (IN), U2.1 (IN), U2.3 (EN)

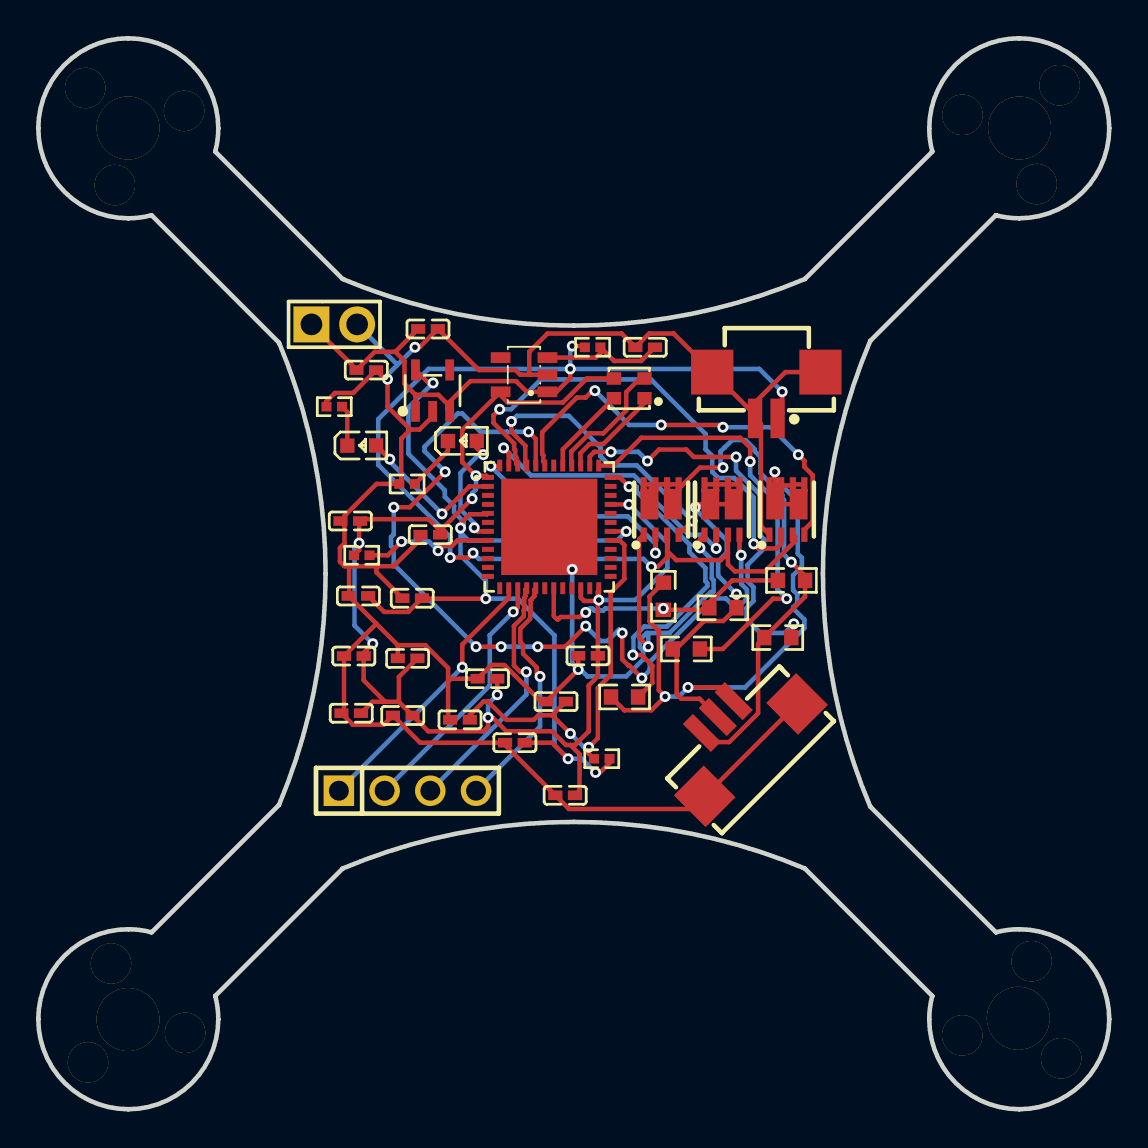
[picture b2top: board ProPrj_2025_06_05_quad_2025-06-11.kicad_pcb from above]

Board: 2 copper layers, 59.5 x 59.5 mm, 41 parts (0 on the bottom side), 31 nets.
